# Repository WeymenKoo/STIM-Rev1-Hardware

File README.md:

<!-- Claude: before every commit or push to this repo, update this README first (status line and date, folder table, anything that moved or was added). It is the only project-level document the team and the client read here; keep it short and factual. -->

# STIM Rev 1 hardware (JY063)

UBC ELEC 491 capstone, project JY063. One channel of a four-channel electrical vestibular stimulator:
a ±100 V bootstrapped Howland current pump (the client's STIM board) and our Rev 1 bench prototype of it.

**Status 2026-11-08.** Client-board LTspice model and acceptance tests A1–A7 simulated; bench measurements at ±30 V in
progress. Rev 1 schematic at 2.1.0-dev (PRELIMINARY): DAC (AD5761R), two ADCs (ADS8689), two ISO7741 isolators
with a bypass header and +5 V / +3.3 V rails added 2026-11-07/08 (sheets 10–13); PCB placed, not routed, not yet updated
from the schematic. Safety protection is planned for Rev 2;
Rev 1 is a bench prototype for dummy loads only, not a safety sign-off.

**Handover note (2026-11-08, Weymen away until about Nov 11).** Everything is in this repository; nothing is pending on a
local machine. If you pick this up:
1. Schematic: `02_rev1_channel/Kicad Projects/STIM_Rev1/` (KiCad 10). Read its `README.md` and the `[Unreleased]`
   block of `CHANGELOG.md` first; `Schematic/STIM_Rev1.pdf` is the current plot, `Report/STIM_Rev1-erc.txt` the
   current ERC (0 errors, 7 known warnings). Next KiCad steps: ERC in the GUI, Update PCB from Schematic, then layout.
2. Open decisions (owner Weymen, do not close without him): DAC range vs RG3 on sheet 6; LCSC numbers still TBD
   (TPS7A4901, 32.4k / 17.8k 0603, 1 uF 0603, 2x8 IDC header); ISO7741FDWR is LCSC/JLCPCB-only stock.
3. FPGA interface for CPEN: `02_rev1_channel/ICD_J3.md` (J3 pinout, three chip selects, read-back scaling).
4. Part sourcing snapshot: `.../STIM_Rev1/Documentation/sourcing_converters_isolators_2026-11-07.csv`.
5. Bench: client-board B0 bring-up records under `01_client_board/tests/B0-bringup/` and `01_client_board/bench/`.
Dates that matter: Rev 1 order target Mon Nov 10, hard cutoff Wed Nov 12 (DR1 Dec 1).

| Folder | What is in it |
|---|---|
| `01_client_board/` | LTspice model of the client's STIM board (`model/`), acceptance tests A1–A7, one folder each (`tests/`), bench rig script and wiring (`bench/`), the sim-vs-bench table (`acceptance-tests.md`), deck 2 (`deck/`) |
| `02_rev1_channel/` | Rev 1 analog channel: KiCad project `Kicad Projects/STIM_Rev1/` (own README and CHANGELOG), design definition, FPGA interface contract `ICD_J3.md`, gate simulations G1/G2 (`tests/`) |
| `03_safety_plan/` | Safety planning for Rev 2: FMEA table, safety-loop architecture and its KiCad sketch, deck 1 |
| `04_demo/` | DR1 demo (Dec 1): FPGA waveform CSV → bench and → simulation, same plots |

**Running a simulation.** Open the `.asc` in LTspice 26.x and run it. Every directive is on the sheet; results are
written to the SPICE error log by `.meas` (View → SPICE Error Log). `.raw` and `.log` outputs are not committed;
rerun to regenerate them. Each test folder has a `RECORD.md` with the question, setup and the sim and bench values.

**Number tags.** [DS] datasheet, [H] hand calculation, [L] LTspice, [N] ngspice, [B] bench, [ASSUME] assumption.

Owner: Weymen Koo. Earlier simulation work (Oct 19–25, 2026) is kept offline and is not part of this repository.

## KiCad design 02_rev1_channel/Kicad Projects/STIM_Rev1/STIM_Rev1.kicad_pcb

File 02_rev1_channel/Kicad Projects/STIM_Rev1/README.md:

# STIM Rev 1 Channel (KiCad project)

+/-100 V INA149 Howland current-pump stimulator channel: the minimal analog path for bench bring-up (Rev 1), trips and
latch return in Rev 2. UBC ELEC 491, JY063. Status: **PRELIMINARY** (rev 2.1.0-dev, 2026-11-07), schematic edits from
`SPICE_SIM/02_rev1_channel/REVIEW_2026-10-27.md` applied (D-H); DAC / ADC / isolator sheets 10-13 populated 2026-11-07; PCB placed, not routed (Update PCB from Schematic pending). Bench prototype, dummy loads
only, not a safety sign-off.

**The KiCad files in this repository are the source.** The first capture was generated from the simulation
repository (SPICE_SIM, `4-rev1-design/05_schematic/tools/gen_schematic.py`), but the schematic has been edited
by hand in KiCad since 2.0.0. Do not re-run the generator over this folder.

Part selection and comparison (PhotoMOS, op amps, DC-DC module, connectors, LED, passive sizing):
`Documentation/STIM_Rev1_Parts_Selection.xlsx`, one sheet per part with a summary and charts above the comparison table.
FPGA interface (J3) contract: `SPICE_SIM/02_rev1_channel/ICD_J3.md` (draft until CPEN signs it; **out of date since 2026-11-04**: J3 is now SPI + ENABLE + 3.3 V, see CHANGELOG).

## Specifications

Tags: [N] ngspice, [L] LTspice, [H] hand calc, [DS] datasheet, [B] bench (none yet).

| Parameter | Rev 1 |
|---|---|
| Output | +/-5 mA, 1 mA/V at DAC_BUF (R7 1.00k). U3 gain = 1 + RF3/RG3: **5.02 with RG3 fitted** (Red Pitaya OUT1/OUT2, +/-1 V), 1 with RG3 DNP (+/-5 V DAC) |
| Command ceiling | G = 1: D3/D4 clamp, ~6.3-7.4 mA. G = 5: U3 output saturation at the +/-9 V LDO rails, ~9 mA. DN2540 limiter behind both |
| Compliance | 5 mA into >= 13 kOhm at a 90 V rail, worst case: 13.15 kOhm [N, model-dependent, archive WS1; margin ~1 %, not yet measured] |
| Rails | +/-100 V nominal (90-110 V) on J1; one +12 V on J2; +/-12 V from U32 (A1212S module); +5V (U46, ADC AVDD) and +3V3 (U47, logic / isolator side 2) from +12V_IN on sheet 13. U32 is an isolated part but its COM is GND; the only barrier is the J3 / isolator one (sheet 10): FPGA ground is isolated from board ground, electrodes are not isolated from the board |
| HV input | F1/F2 0451.500MRL 500 mA 125 VDC (rail-to-rail short at +/-100 V exceeds the rating: open item); RSP/RSN 10 Ohm shunts; C2/C3 1 uF 400 V with R23/R24 200k bleeders (tau 0.2 s) |
| Bench supplies | two 30 V supplies in series, midpoint to GND, bias jumpers JP1/JP2 closed (`02_rev1_channel/rev1-minimal-design-definition.md` §5 [N]) |
| Limiter | DN2540 pair + RLIM1, 6.4-8.8 mA [N]. **M1/M2/RLIM1 DNP at assembly**, paired and fitted at bring-up (R2); JP4 bypasses the limiter until then, never at +/-100 V |
| Switches | two AQY214S PhotoMOS (stimulating U4, return U5) driven by ENABLE (R22 100k pull-down = open). JP5/JP6 bypass them (OFF by default); with ENABLE low an ammeter across JP5 measures the stimulating-line current |
| Read-back | I_RETURN_ADC = VMID + 0.2 V/mA; V_ELEC_ADC = VMID + V_elec/101; VMID_REF 1.66 V; read by two ADS8689 (16-bit, 0-5.12 V range): U41 on I_RETURN_ADC, U42 on V_ELEC_ADC, sheet 12. VMID_REF is measured once on TP29, not digitised |
| FPGA connector J3 | 2x8 IDC: 1 +3V3_FPGA, 3 SPI_SCLK, 5 SPI_MOSI, 7 SPI_MISO, 9 SPI_CS_DAC, 11 SPI_CS_ADC, 13 ENABLE, 15 SPI_CS_ADC2, even pins GND_FPGA. Isolated by U43 ISO7741FDWR (ENABLE, SCLK, MOSI; default low) and U44 ISO7741DWR (CS_DAC, CS_ADC, CS_ADC2, MISO back; default high); J5 is the board-side twin for the JP7 bypass; one spare reverse channel (FAULT_N, TP38). `ICD_J3.md` rewritten 2026-11-07 |
| Command DAC | U40 AD5761RBRUZ, +/-5 V range on +/-12 V, 2.5 V internal reference, SPI shared with the ADC (CS_DAC); DAC_CMD +/-5 V -> RG3 DNP (G = 1) or range +/-3 V with RG3 fitted (open) |
| Board | JLCPCB 4-layer JLC04161H-7628, 1.6 mm, Economic PCBA (top side). Target outline <= 100 x 100 mm (4-layer promo tier) |
| Parts | 175 references: 133 parts (M1, M2, RLIM1 DNP), 38 test loops (TP2, TP4-TP40), 4 mounting holes. Power sheets 3, 4 and 13 export their rails as ports; the rail symbols sit on the cover. Extended-part types added 2026-11-07/08: ISO7741DWR, ISO7741FDWR, AD5761RBRUZ, ADS8689IPWR (4); TPS7A4901 reused |

## Pages

1. Doc - Cover (`STIM_Rev1.kicad_sch`)
2. Doc - Revision History (`revision-history.kicad_sch`)
3. Power - HV Input & Fusing (`power-hv-input.kicad_sch`)
4. Power - Aux Input & +/-9 V LDOs (`power-aux-input.kicad_sch`)
5. Interface - FPGA (`interface-fpga.kicad_sch`)
6. Analog - Input Clamp & Buffer (`analog-clamp-buffer.kicad_sch`)
7. Analog - Howland Current Pump (`analog-current-pump.kicad_sch`)
8. Output - Limiter & PhotoMOS (`output-limiter-photomos.kicad_sch`)
9. Sense - Feedback to ADC (`sense-feedback-adc.kicad_sch`)
10. Interface - SPI Isolator (`interface-spi-isolator.kicad_sch`) - U43/U44 ISO7741, J5 bypass header, JP7
11. Interface - DAC Command (`interface-dac-command.kicad_sch`) - U40 AD5761R
12. Interface - ADC Read-back (`interface-adc-readback.kicad_sch`) - U41 / U42 ADS8689 (I and V)
13. Power - Converter Rails (`power-converter-rails.kicad_sch`) - U46 +5V, U47 +3V3

## Directory structure

```
STIM_Rev1
├── CHANGELOG.md     # Keep a Changelog; the Revision History page is generated from it
├── Templates        # KDT_Template_GIT.kicad_wks title block (nguyen-v/KDT_Hierarchical_KiBot, MIT)
├── Report           # ERC report (DRC after layout)
├── Testing/Testpoints   # test-point tables (after layout)
├── lib
│   ├── lib_sym      # STIM_Rev1.kicad_sym: every symbol of the design
│   ├── lib_fp       # STIM_Rev1.pretty: every footprint of the design
│   └── 3d_models    # STEP models
├── Simulation
│   ├── models       # SPICE models used by the symbols' simulation fields
│   └── figures      # simulation figures
├── Computations     # rev1_hand_calcs.md (the Oct 24 PDF is in _archive/)
├── Documentation    # parts selection workbook (xlsx), sourcing snapshots (csv)
├── tools            # one-shot generator that drew sheets 10-13 (record only, do not re-run)
├── Schematic        # PDF of the schematic
├── Manufacturing
│   ├── Assembly     # BoM, CPL (after layout, Fabrication Toolkit)
│   └── Fabrication  # Gerbers, drill (after layout)
└── Images           # renders
```

## Design rules

4-layer JLCPCB stackup and HV rules in `STIM_Rev1.kicad_dru`, with sources: SPICE_SIM `4-rev1-design/07_pcb/design-rules-research.md`.

## Format and versioning

Layout follows the EPFL Xplore AMULET controller schematics and the KDT_Hierarchical_KiBot template by the same
author (https://github.com/nguyen-v/KDT_Hierarchical_KiBot): folder tree, title block (`Templates/`, MIT licence
alongside), text variables (`PROJECT_NAME`, `BOARD_NAME`, `COMPANY`, `DESIGNER`, `VARIANT`, `REVISION`,
`RELEASE_DATE`, `SHEET_NAME_n`, `RELEASE_TITLE_x` / `RELEASE_BODY_x`), `CHANGELOG.md` with an `[Unreleased]`
section, and the variant vocabulary DRAFT / PRELIMINARY / CHECKED / RELEASED. Versions are semantic versioning
applied to hardware (https://www.maskset.net/blog/2023/02/26/semantic-versioning-for-hardware/): MAJOR incompatible
interface or form factor, MINOR compatible circuit / BoM / stackup change, PATCH documentation only. KiBot CI from the
template is not set up here.

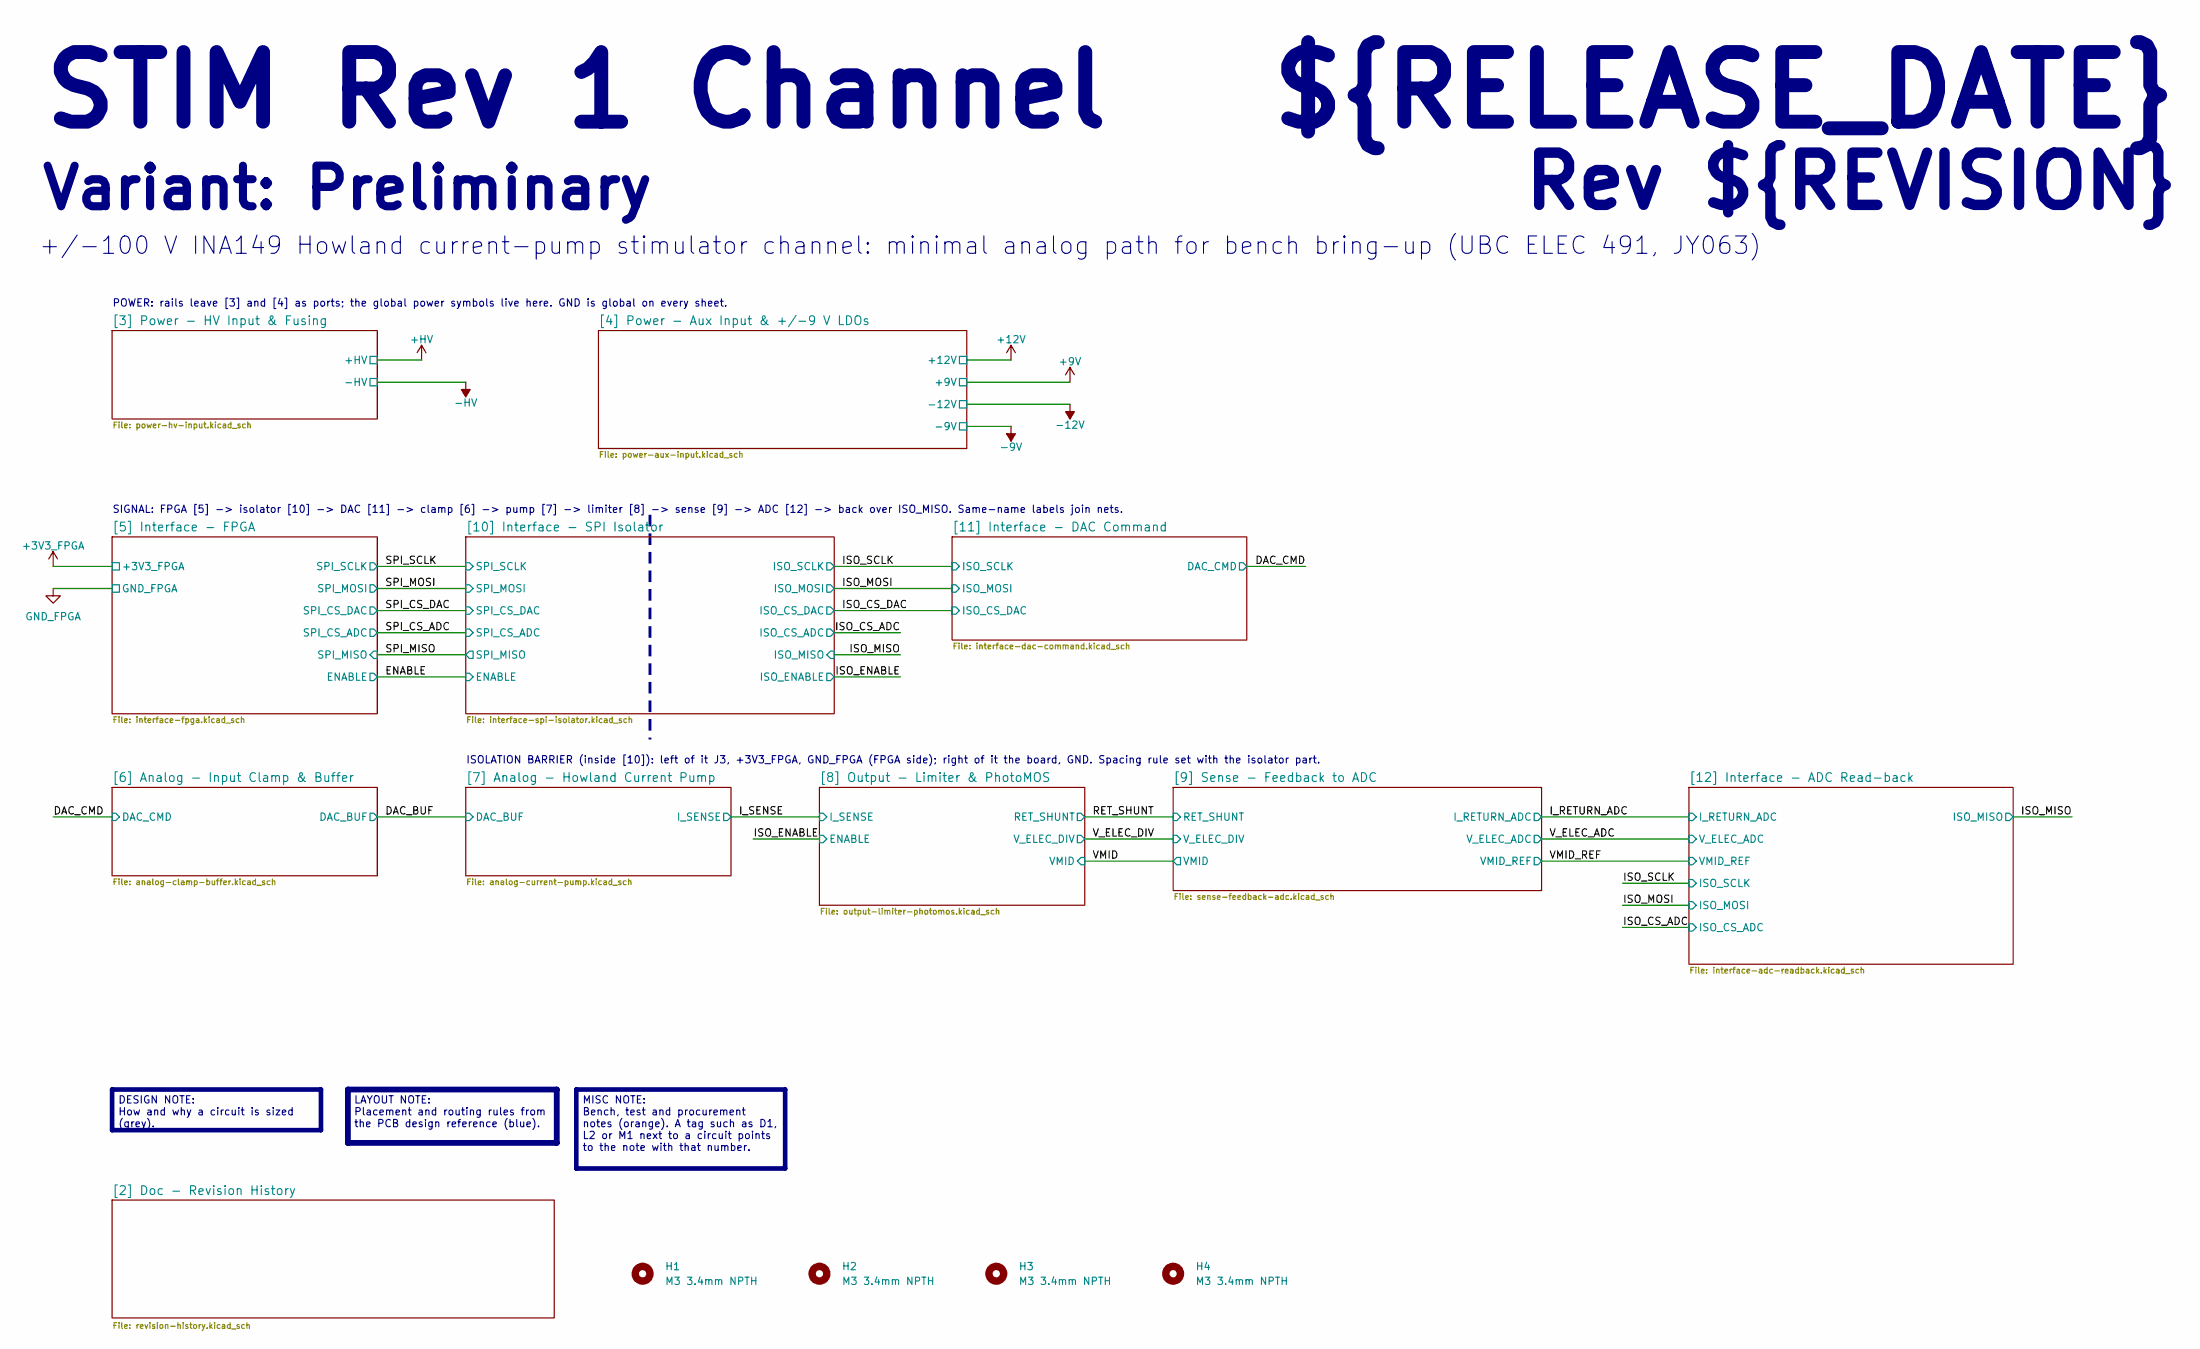
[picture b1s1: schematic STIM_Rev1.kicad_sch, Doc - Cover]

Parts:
H1, H2, H3, H4: M3 3.4mm NPTH; MountingHole_3.4mm_M3_Keepout6.5mm

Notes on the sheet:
Variant: Preliminary
${RELEASE_DATE}
STIM Rev 1 Channel
+/-100 V INA149 Howland current-pump stimulator channel: minimal analog path for bench bring-up (UBC ELEC 491, JY063)
Rev ${REVISION}
MISC NOTE: Bench, test and procurement notes (orange). A tag such as D1, L2 or M1 next to a circuit points to the note with that number.
LAYOUT NOTE: Placement and routing rules from the PCB design reference (blue).
DESIGN NOTE: How and why a circuit is sized (grey).
POWER: rails leave [3] and [4] as ports; the global power symbols live here. GND is global on every sheet.
ISOLATION BARRIER (inside [10]): left of it J3, +3V3_FPGA, GND_FPGA (FPGA side); right of it the board, GND. Spacing rule set with the isolator part.
SIGNAL: FPGA [5] -> isolator [10] -> DAC [11] -> clamp [6] -> pump [7] -> limiter [8] -> sense [9] -> ADC [12] -> back over ISO_MISO. Same-name labels join nets.

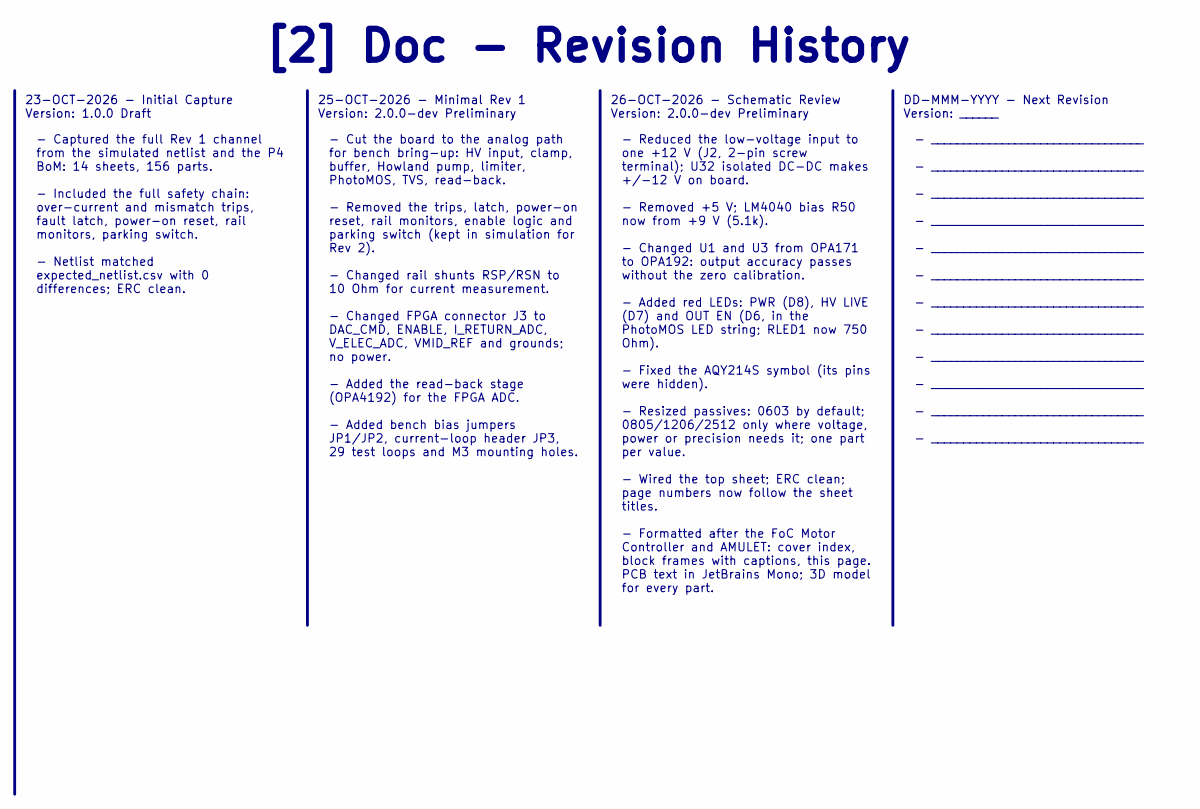
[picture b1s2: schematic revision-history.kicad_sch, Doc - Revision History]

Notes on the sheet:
23-OCT-2026 - Initial Capture Version: 1.0.0 Draft
25-OCT-2026 - Minimal Rev 1 Version: 2.0.0-dev Preliminary
- Cut the board to the analog path for bench bring-up: HV input, clamp, buffer, Howland pump, limiter, PhotoMOS, TVS, read-back. - Removed the trips, latch, power-on reset, rail monitors, enable logic and parking switch (kept in simulation for Rev 2). - Changed rail shunts RSP/RSN to 10 Ohm for cur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
26-OCT-2026 - Schematic Review Version: 2.0.0-dev Preliminary
[2] Doc - Revision History
- _________________________________ - _________________________________ - _________________________________ - _________________________________ - _________________________________ - _________________________________ - _________________________________ - _________________________________ - _________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
DD-MMM-YYYY - Next Revision Version: ______
- Captured the full Rev 1 channel from the simulated netlist and the P4 BoM: 14 sheets, 156 parts. - Included the full safety chain: over-current and mismatch trips, fault latch, power-on reset, rail monitors, parking switch. - Netlist matched expected_netlist.csv with 0 differences; ERC clean.
- Reduced the low-voltage input to one +12 V (J2, 2-pin screw terminal); U32 isolated DC-DC makes +/-12 V on board. - Removed +5 V; LM4040 bias R50 now from +9 V (5.1k). - Changed U1 and U3 from OPA171 to OPA192: output accuracy passes without the zero calibration. - Added red LEDs: PWR (D8), HV LI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

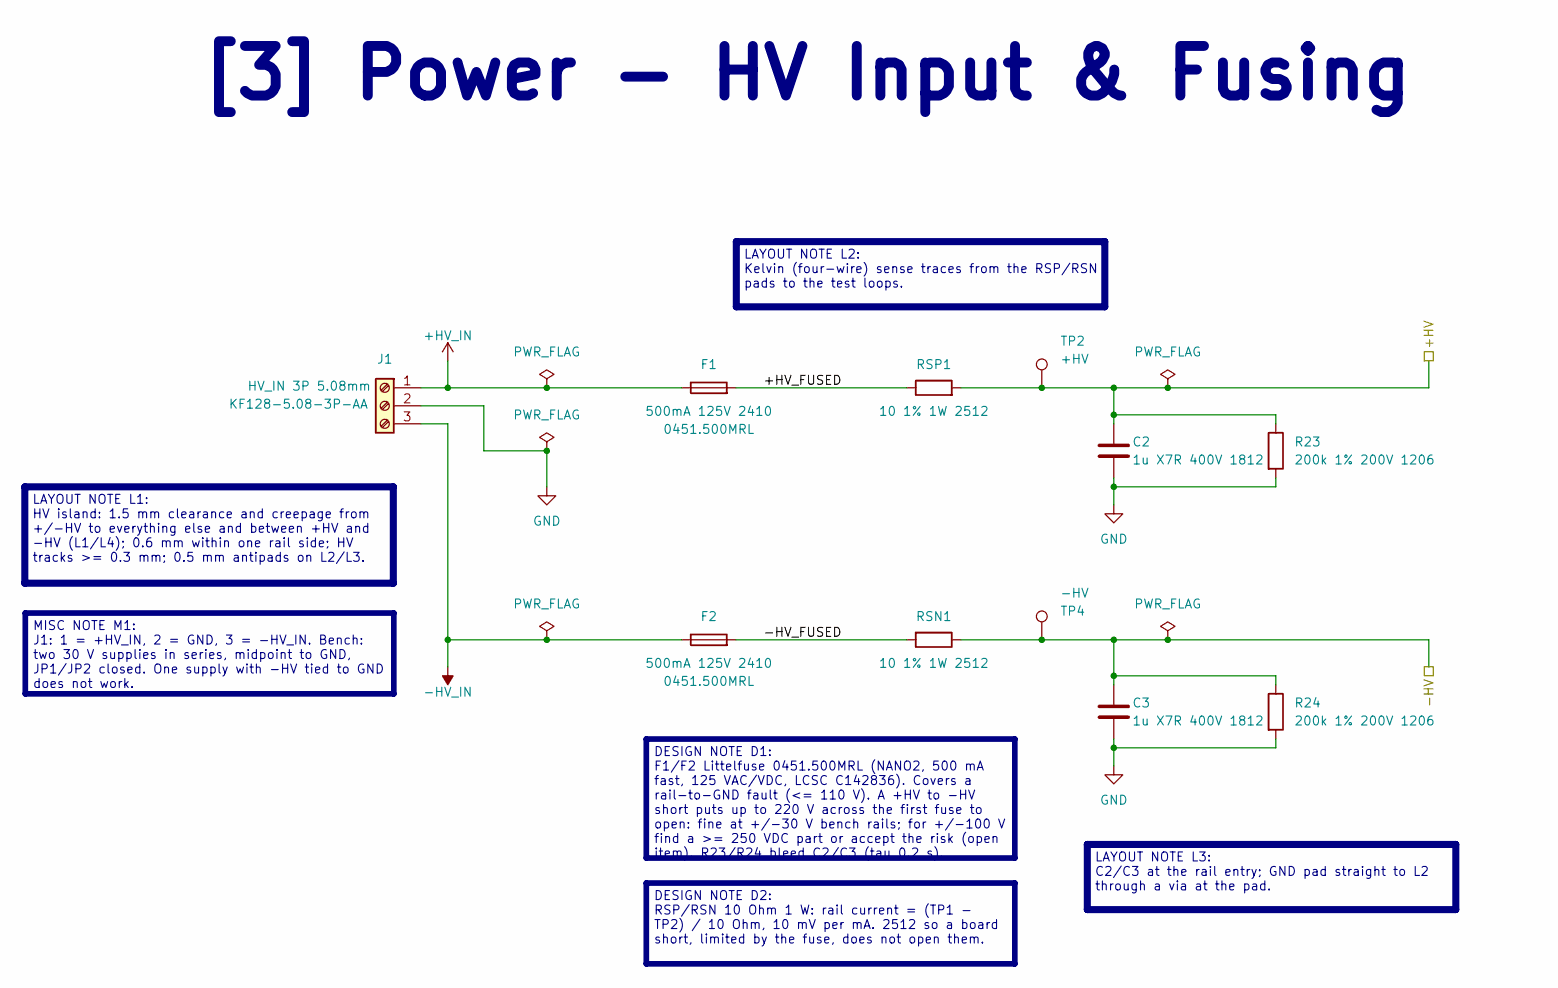
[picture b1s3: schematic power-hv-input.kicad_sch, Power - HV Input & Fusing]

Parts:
C2, C3: 1u X7R 400V 1812; C_1812_4532Metric; MPN FE2CX105M501LFL; LCSC C19267793
F1, F2: 500mA 125V 2410; Fuse_2410_6125Metric_SST; MPN 0451.500MRL; LCSC C142836
J1: HV_IN 3P 5.08mm; TerminalBlock_Phoenix_MKDS-1,5-3-5.08_1x03_P5.08mm_Horizont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; MPN KF128-5.08-3P-AA; LCSC C474953
R23, R24: 200k 1% 200V 1206; R_1206_3216Metric; MPN 1206W4F2003T5E; LCSC C17954
RSN1: 10 1% 1W 2512; R_2512_6332Metric; MPN 25121WF100JT4E; LCSC C47019
RSP1: 10 1% 1W 2512; R_2512_6332Metric; MPN 25121WF100JT4E; LCSC C47019
TP2: +HV; TestPoint_Keystone_5000-5004_Miniature
TP4: -HV; TestPoint_Keystone_5000-5004_Miniature

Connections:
+HV: C2.1, R23.1, RSP1.2, TP2.1 (1_1); also elsewhere on the board
+HV_IN: F1.1, J1.1; also elsewhere on the board
-HV: C3.1, R24.1, RSN1.1, TP4.1 (1_1); also elsewhere on the board
-HV_IN: F2.1, J1.3; also elsewhere on the board
/[3] Power - HV Input & Fusing/+HV_FUSED: F1.2, RSP1.1
/[3] Power - HV Input & Fusing/-HV_FUSED: F2.2, RSN1.2

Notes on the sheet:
[3] Power - HV Input & Fusing
DESIGN NOTE D1: F1/F2 Littelfuse 0451.500MRL (NANO2, 500 mA fast, 125 VAC/VDC, LCSC C142836). Covers a rail-to-GND fault (<= 110 V). A +HV to -HV short puts up to 220 V across the first fuse to open: fine at +/-30 V bench rails; for +/-100 V find a >= 250 VDC part or accept the risk (open item). R2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
DESIGN NOTE D2: RSP/RSN 10 Ohm 1 W: rail current = (TP1 - TP2) / 10 Ohm, 10 mV per mA. 2512 so a board short, limited by the fuse, does not open them.
LAYOUT NOTE L1: HV island: 1.5 mm clearance and creepage from +/-HV to everything else and between +HV and -HV (L1/L4); 0.6 mm within one rail side; HV tracks >= 0.3 mm; 0.5 mm antipads on L2/L3.
LAYOUT NOTE L3: C2/C3 at the rail entry; GND pad straight to L2 through a via at the pad.
LAYOUT NOTE L2: Kelvin (four-wire) sense traces from the RSP/RSN pads to the test loops.
MISC NOTE M1: J1: 1 = +HV_IN, 2 = GND, 3 = -HV_IN. Bench: two 30 V supplies in series, midpoint to GND, JP1/JP2 closed. One supply with -HV tied to GND does not work.

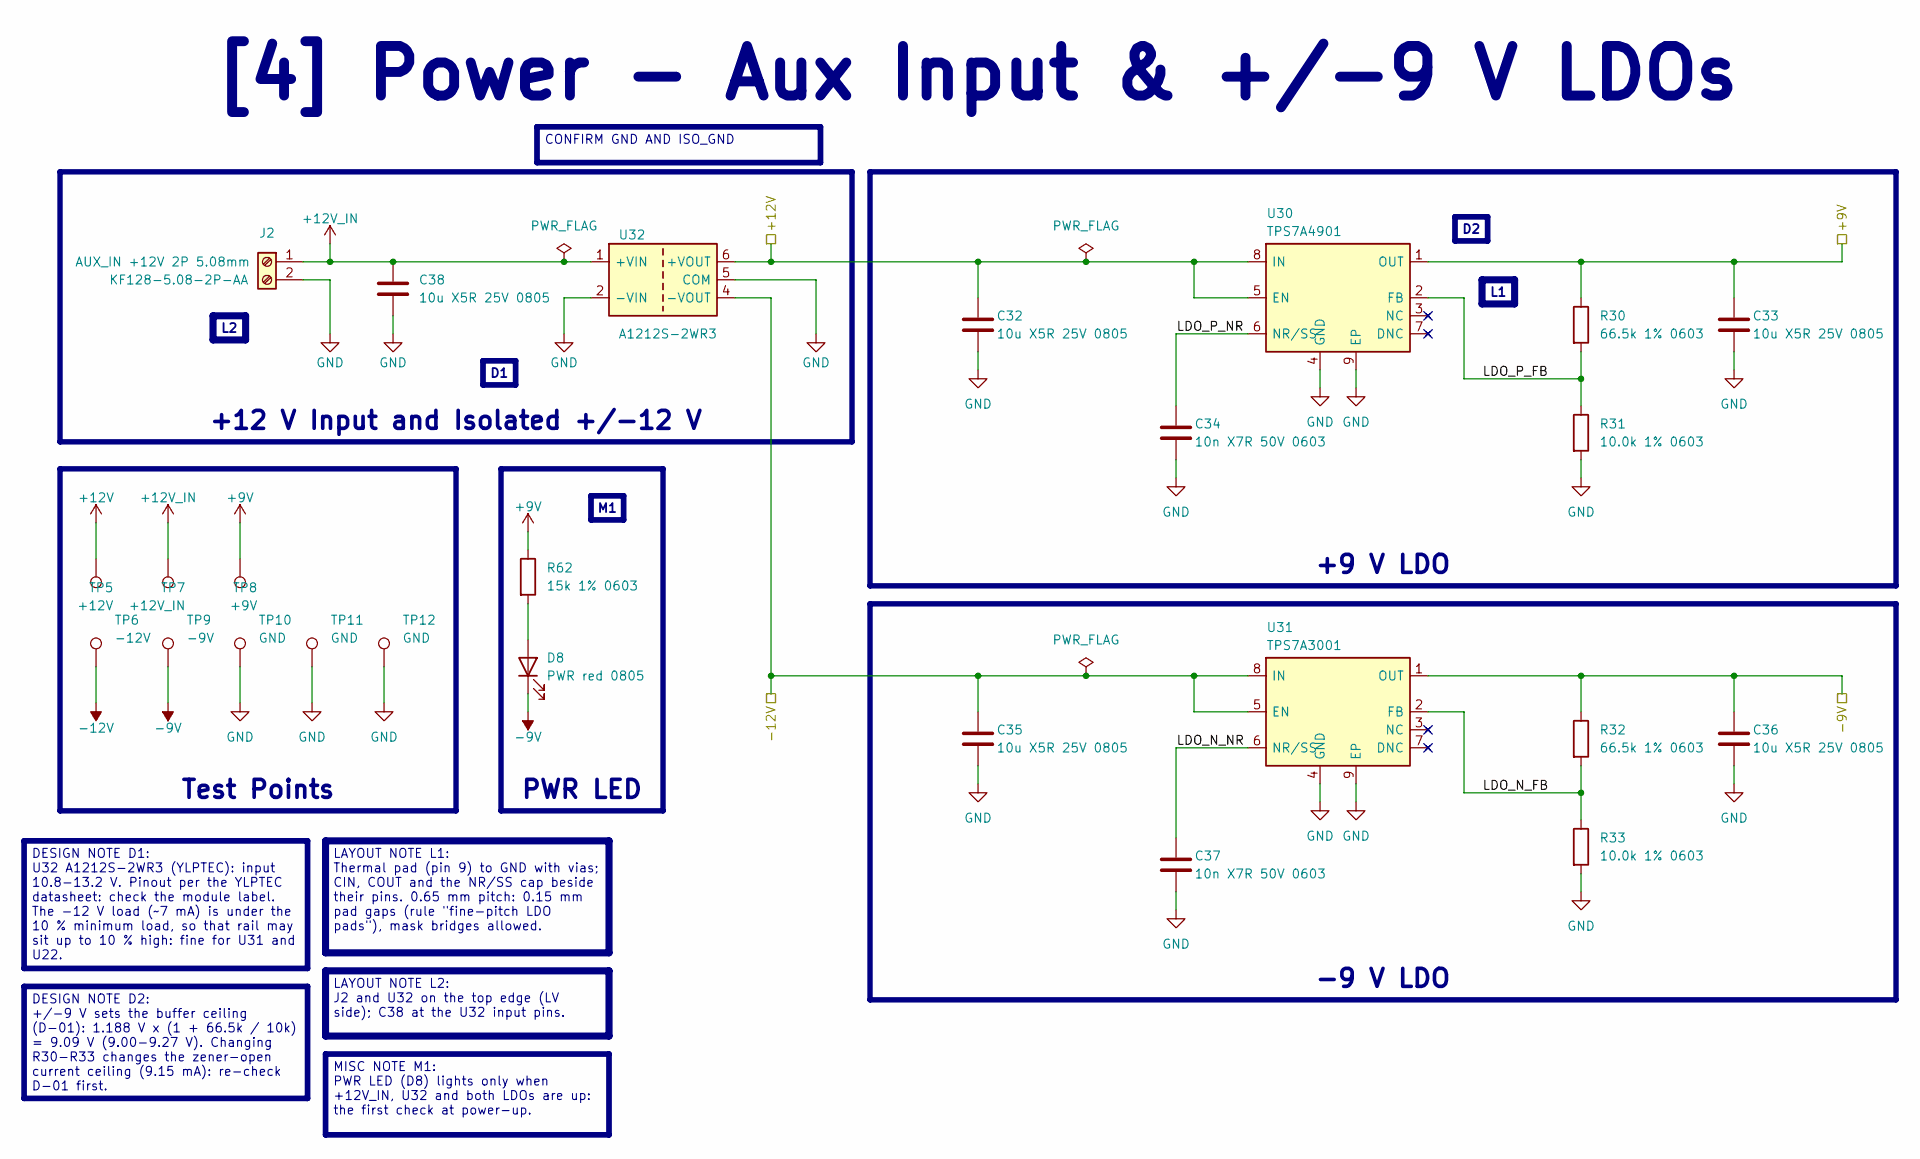
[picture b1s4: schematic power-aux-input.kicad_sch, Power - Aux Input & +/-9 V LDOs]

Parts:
C32, C33, C35, C36, C38: 10u X5R 25V 0805; C_0805_2012Metric; MPN CL21A106KAYNNNE; LCSC C15850
C34, C37: 10n X7R 50V 0603; C_0603_1608Metric; MPN CL10B103KB8NNNC; LCSC C1589
D8: PWR red 0805; LED_0805_2012Metric; MPN NCD0805R1; LCSC C84256
J2: AUX_IN +12V 2P 5.08mm; TerminalBlock_Phoenix_MKDS-1,5-2-5.08_1x02_P5.08mm_Horizont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; MPN KF128-5.08-2P-AA; LCSC C474952
R30, R32: 66.5k 1% 0603; R_0603_1608Metric; MPN 0603WAF6652T5E; LCSC C23225
R31, R33: 10.0k 1% 0603; R_0603_1608Metric; MPN 0603WAF1002T5E; LCSC C25804
R62: 15k 1% 0603; R_0603_1608Metric; MPN 0603WAF1502T5E; LCSC C22809
TP5: +12V; TestPoint_Keystone_5000-5004_Miniature
TP6: -12V; TestPoint_Keystone_5000-5004_Miniature
TP7: +12V_IN; TestPoint_Keystone_5000-5004_Miniature
TP8: +9V; TestPoint_Keystone_5000-5004_Miniature
TP9: -9V; TestPoint_Keystone_5000-5004_Miniature
TP10, TP11, TP12: GND; TestPoint_Keystone_5000-5004_Miniature
U30: TPS7A4901; Texas_DGN0008D_VSSOP-8-1EP_3x3mm_P0.65mm_EP2x2.94mm_Mask1.5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
U31: TPS7A3001; Texas_DGN0008D_VSSOP-8-1EP_3x3mm_P0.65mm_EP2x2.94mm_Mask1.5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
U32: A1212S-2WR3; Converter_DCDC_A_S-2WR3_SIP-6_P2.54mm; MPN A1212S-2WR3; LCSC C5369434

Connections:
+9V: C33.1, R30.1, R62.1, TP8.1 (1_1), U30.1 (OUT); also elsewhere on the board
+12V: C32.1, TP5.1 (1_1), U30.5 (EN), U30.8 (IN), U32.6 (+VOUT); also elsewhere on the board
+12V_IN: C38.1, J2.1, TP7.1 (1_1), U32.1 (+VIN)
-9V: C36.1, D8.1 (K), R32.1, TP9.1 (1_1), U31.1 (OUT); also elsewhere on the board
-12V: C35.1, TP6.1 (1_1), U31.5 (EN), U31.8 (IN), U32.4 (-VOUT); also elsewhere on the board
/[4] Power - Aux Input & +/-9 V LDOs/LDO_N_FB: R32.2, R33.1, U31.2 (FB)
/[4] Power - Aux Input & +/-9 V LDOs/LDO_N_NR: C37.1, U31.6 (NR/SS)
/[4] Power - Aux Input & +/-9 V LDOs/LDO_P_FB: R30.2, R31.1, U30.2 (FB)
/[4] Power - Aux Input & +/-9 V LDOs/LDO_P_NR: C34.1, U30.6 (NR/SS)
unnamed: D8.2 (A), R62.2

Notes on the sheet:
Test Points
PWR LED
-9 V LDO
CONFIRM GND AND ISO_GND
+9 V LDO
LAYOUT NOTE L1: Thermal pad (pin 9) to GND with vias; CIN, COUT and the NR/SS cap beside their pins. 0.65 mm pitch: 0.15 mm pad gaps (rule "fine-pitch LDO pads"), mask bridges allowed.
LAYOUT NOTE L2: J2 and U32 on the top edge (LV side); C38 at the U32 input pins.
DESIGN NOTE D1: U32 A1212S-2WR3 (YLPTEC): input 10.8-13.2 V. Pinout per the YLPTEC datasheet: check the module label. The -12 V load (~7 mA) is under the 10 % minimum load, so that rail may sit up to 10 % high: fine for U31 and U22.
MISC NOTE M1: PWR LED (D8) lights only when +12V_IN, U32 and both LDOs are up: the first check at power-up.
DESIGN NOTE D2: +/-9 V sets the buffer ceiling (D-01): 1.188 V x (1 + 66.5k / 10k) = 9.09 V (9.00-9.27 V). Changing R30-R33 changes the zener-open current ceiling (9.15 mA): re-check D-01 first.
[4] Power - Aux Input & +/-9 V LDOs
+12 V Input and Isolated +/-12 V

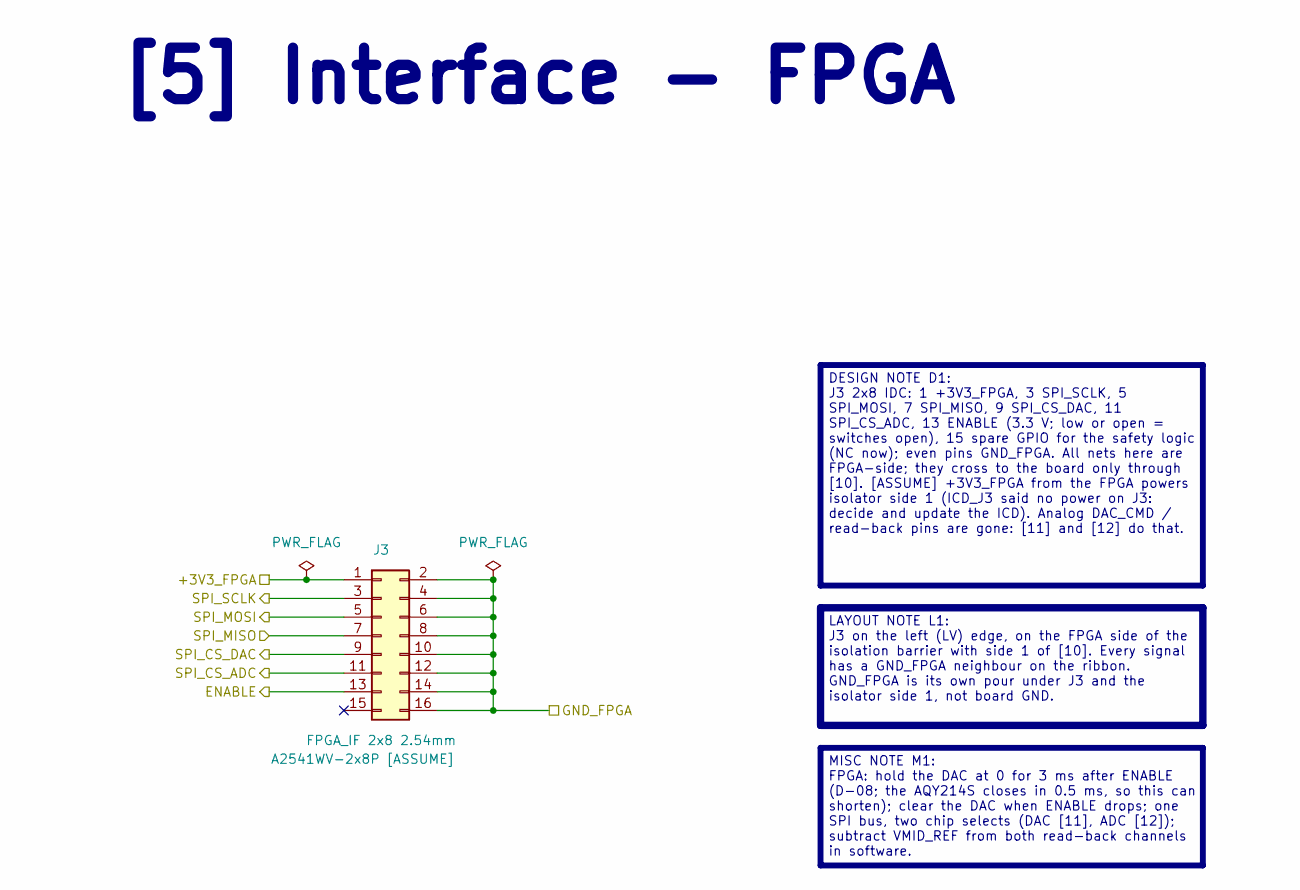
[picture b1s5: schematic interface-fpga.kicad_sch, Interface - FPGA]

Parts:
J3: FPGA_IF 2x8 2.54mm; IDC-Header_2x08_P2.54mm_Vertical; MPN A2541WV-2x8P [ASSUME]; JLC Extended

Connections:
/ENABLE: J3.3; also elsewhere on the board
/I_RETURN_ADC: J3.5; also elsewhere on the board
/VMID_REF: J3.9; also elsewhere on the board
/V_ELEC_ADC: J3.7; also elsewhere on the board

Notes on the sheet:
[5] Interface - FPGA
LAYOUT NOTE L1: J3 on the left (LV) edge, on the FPGA side of the isolation barrier with side 1 of [10]. Every signal has a GND_FPGA neighbour on the ribbon. GND_FPGA is its own pour under J3 and the isolator side 1, not board GND.
DESIGN NOTE D1: J3 2x8 IDC: 1 +3V3_FPGA, 3 SPI_SCLK, 5 SPI_MOSI, 7 SPI_MISO, 9 SPI_CS_DAC, 11 SPI_CS_ADC, 13 ENABLE (3.3 V; low or open = switches open), 15 spare GPIO for the safety logic (NC now); even pins GND_FPGA. All nets here are FPGA-side; they cross to the board only through [10]. [ASSUME]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
MISC NOTE M1: FPGA: hold the DAC at 0 for 3 ms after ENABLE (D-08; the AQY214S closes in 0.5 ms, so this can shorten); clear the DAC when ENABLE drops; one SPI bus, two chip selects (DAC [11], ADC [12]); subtract VMID_REF from both read-back channels in software.

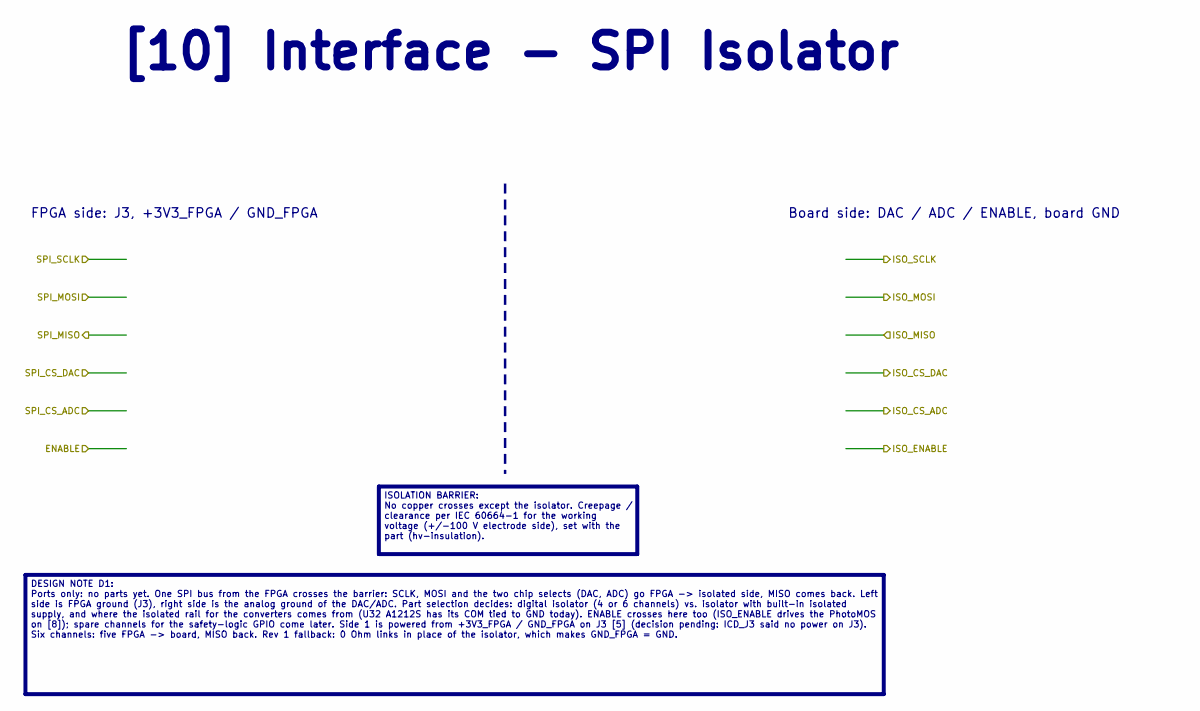
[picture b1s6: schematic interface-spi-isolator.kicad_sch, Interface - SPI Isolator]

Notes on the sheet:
ISOLATION BARRIER: No copper crosses except the isolator. Creepage / clearance per IEC 60664-1 for the working voltage (+/-100 V electrode side), set with the part (hv-insulation).
FPGA side: J3, +3V3_FPGA / GND_FPGA
Board side: DAC / ADC / ENABLE, board GND
DESIGN NOTE D1: Ports only: no parts yet. One SPI bus from the FPGA crosses the barrier: SCLK, MOSI and the two chip selects (DAC, ADC) go FPGA -> isolated side, MISO comes back. Left side is FPGA ground (J3), right side is the analog ground of the DAC/ADC. Part selection decides: digital isolator 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
[10] Interface - SPI Isolator

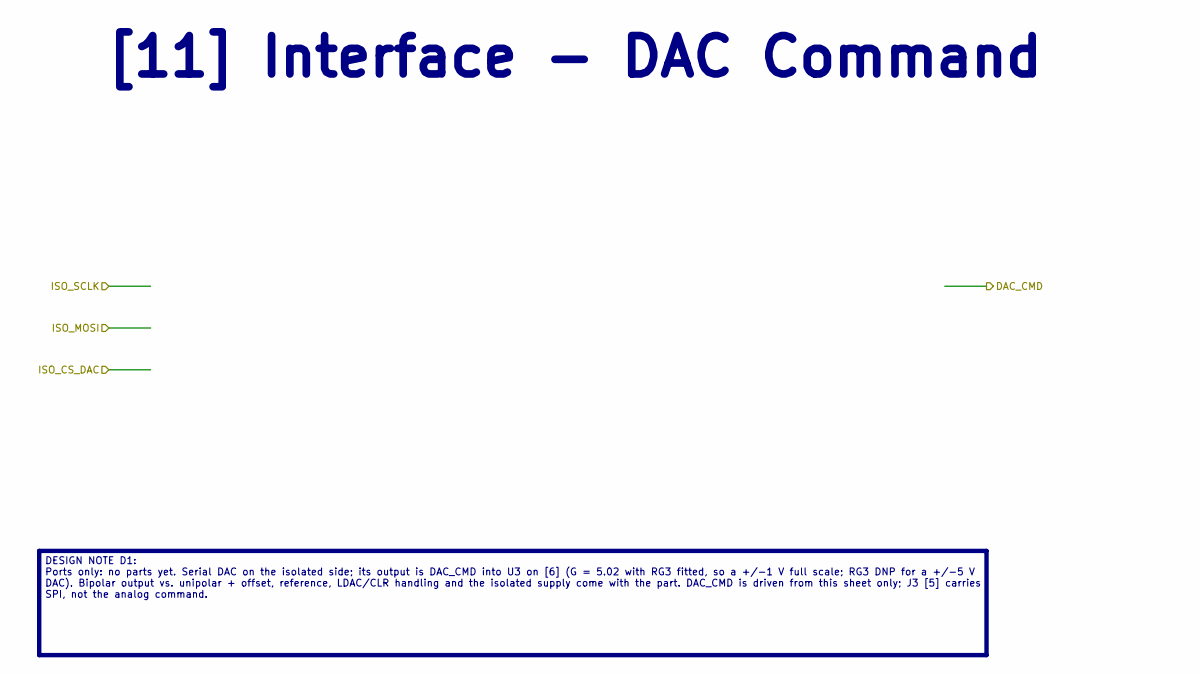
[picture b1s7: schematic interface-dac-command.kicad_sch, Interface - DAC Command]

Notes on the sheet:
[11] Interface - DAC Command
DESIGN NOTE D1: Ports only: no parts yet. Serial DAC on the isolated side; its output is DAC_CMD into U3 on [6] (G = 5.02 with RG3 fitted, so a +/-1 V full scale; RG3 DNP for a +/-5 V DAC). Bipolar output vs. unipolar + offset, reference, LDAC/CLR handling and the isolated supply come with the part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

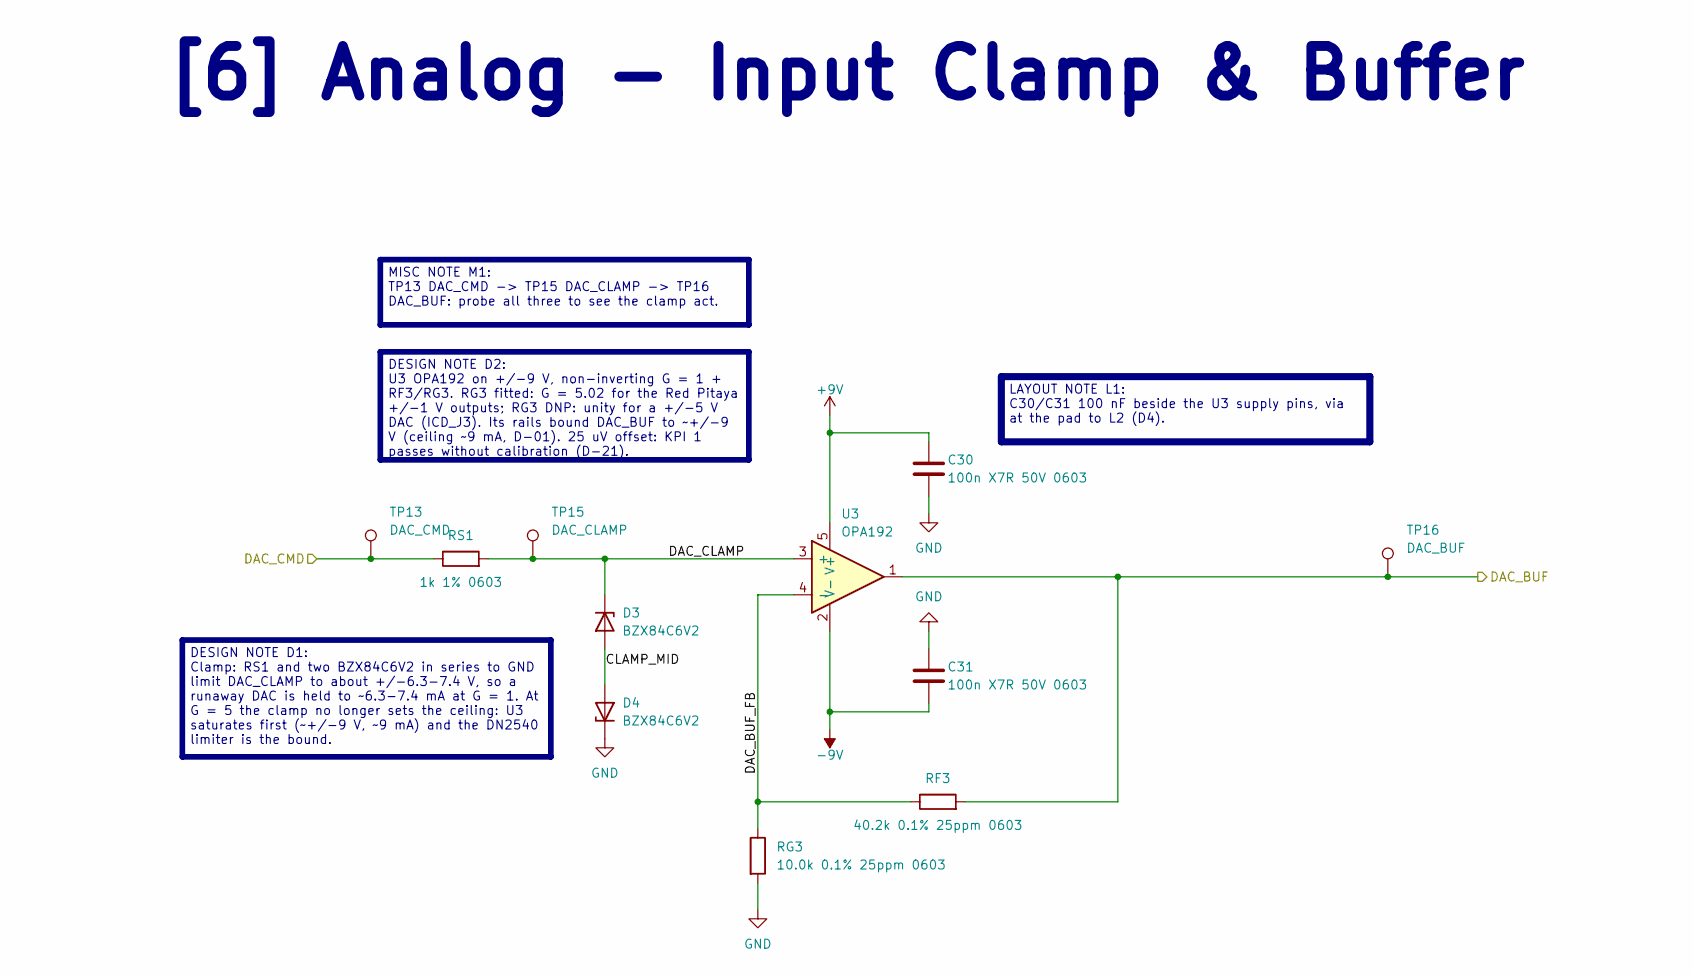
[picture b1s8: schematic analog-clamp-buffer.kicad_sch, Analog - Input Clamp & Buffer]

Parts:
C30, C31: 100n X7R 50V 0603; C_0603_1608Metric; MPN CL10B104KB8NNNC; LCSC C1591
D3, D4: BZX84C6V2; SOT-23; MPN BZX84C6V2LT1G; LCSC C82470
RF3: 40.2k 0.1% 25ppm 0603; R_0603_1608Metric; MPN RT0603BRD0740K2L; LCSC C723489
RG3: 10.0k 0.1% 25ppm 0603; R_0603_1608Metric; MPN RT0603BRD0710KL; LCSC C95204
RS1: 1k 1% 0603; R_0603_1608Metric; MPN 0603WAF1001T5E; LCSC C21190
TP13: DAC_CMD; TestPoint_Keystone_5000-5004_Miniature
TP15: DAC_CLAMP; TestPoint_Keystone_5000-5004_Miniature
TP16: DAC_BUF; TestPoint_Keystone_5000-5004_Miniature
U3: OPA192; SOT-23-5; MPN OPA192IDBVR; LCSC C139648

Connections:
+9V: C30.1, U3.5 (V+); also elsewhere on the board
-9V: C31.1, U3.2 (V-); also elsewhere on the board
/DAC_BUF: RF3.2, TP16.1 (1_1), U3.1; also elsewhere on the board
/[6] Analog - Input Clamp & Buffer/CLAMP_MID: D3.1 (A), D4.1 (A)
/[6] Analog - Input Clamp & Buffer/DAC_BUF_FB: RF3.1, RG3.1, U3.4 (-)
/[6] Analog - Input Clamp & Buffer/DAC_CLAMP: D3.3 (K), RS1.2, TP15.1 (1_1), U3.3 (+)

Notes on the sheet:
[6] Analog - Input Clamp & Buffer
LAYOUT NOTE L1: C30/C31 100 nF beside the U3 supply pins, via at the pad to L2 (D4).
DESIGN NOTE D1: Clamp: RS1 and two BZX84C6V2 in series to GND limit DAC_CLAMP to about +/-6.3-7.4 V, so a runaway DAC is held to ~6.3-7.4 mA at G = 1. At G = 5 the clamp no longer sets the ceiling: U3 saturates first (~+/-9 V, ~9 mA) and the DN2540 limiter is the bound.
MISC NOTE M1: TP13 DAC_CMD -> TP15 DAC_CLAMP -> TP16 DAC_BUF: probe all three to see the clamp act.
DESIGN NOTE D2: U3 OPA192 on +/-9 V, non-inverting G = 1 + RF3/RG3. RG3 fitted: G = 5.02 for the Red Pitaya +/-1 V outputs; RG3 DNP: unity for a +/-5 V DAC (ICD_J3). Its rails bound DAC_BUF to ~+/-9 V (ceiling ~9 mA, D-01). 25 uV offset: KPI 1 passes without calibration (D-21).

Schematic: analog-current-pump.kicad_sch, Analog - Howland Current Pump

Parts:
C1: 100n X7R 250V 1206; C_1206_3216Metric; MPN TCC1206X7R104M251FT; LCSC C282822
C40: 100n X7R 50V 0603; C_0603_1608Metric; MPN CL10B104KB8NNNC; LCSC C1591
D1, D2: BAS16; SOT-23; MPN BAS16 A6; LCSC C8489
JP1, JP2: JP 1x2; PinHeader_1x02_P2.54mm_Vertical
Q1: MJD350; TO-252-2; MPN MJD350-13; LCSC C460225
Q2: MJD340; TO-252-2; MPN MJD340-13; LCSC C443830
R1, R2, R5, R6: 44.2k 1% 200V 1206; R_1206_3216Metric; MPN CL1206FN44K2PS; LCSC C53284084
R3, R4: 14.3k 1% 0805; R_0805_2012Metric; MPN 0805W8F1432T5E; LCSC C17456
R7: 1.00k 0.1% 25ppm 0805; R_0805_2012Metric; MPN RT0805BRD071KL; LCSC C110774
RB1, RB2: 41.2k 1% 200V 1206; R_1206_3216Metric; MPN 1206W4F4122T5E; LCSC C247267
TP17: PUMP_OUT; TestPoint_Keystone_5000-5004_Miniature
TP18: PUMP_REF; TestPoint_Keystone_5000-5004_Miniature
TP19, TP20: PUMP_V+; TestPoint_Keystone_5000-5004_Miniature
TP21: I_SENSE; TestPoint_Keystone_5000-5004_Miniature
U1: OPA192; SOT-23-5; MPN OPA192IDBVR; LCSC C139648
U2: INA149; SOIC-8_3.9x4.9mm_P1.27mm; MPN INA149AIDR; LCSC C183089

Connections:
+HV: JP1.1 (A), Q2.2 (C), R1.1; also elsewhere on the board
-HV: JP2.2 (B), Q1.2 (C), R6.2; also elsewhere on the board
/DAC_BUF: U2.3 (+IN); also elsewhere on the board
/[7] Analog - Howland Current Pump/BENCH_BIAS_N: JP2.1 (A), RB2.1
/[7] Analog - Howland Current Pump/BENCH_BIAS_P: JP1.2 (B), RB1.1
/[7] Analog - Howland Current Pump/BIAS_D2_R4: D2.3 (K), R4.1
/[7] Analog - Howland Current Pump/BIAS_R1_R2: R1.2, R2.1
/[7] Analog - Howland Current Pump/BIAS_R3_D1: D1.1 (A), R3.2
/[7] Analog - Howland Current Pump/BIAS_R5_R6: R5.2, R6.1
/[7] Analog - Howland Current Pump/I_SENSE: R7.2, TP21.1 (1_1), U1.3 (+); also elsewhere on the board
/[7] Analog - Howland Current Pump/PUMP_OUT: D1.3 (K), D2.1 (A), R7.1, TP17.1 (1_1), U2.6 (VOUT); also elsewhere on the board
/[7] Analog - Howland Current Pump/PUMP_REF: TP18.1 (1_1), U1.1, U1.4 (-), U2.1 (REF_B), U2.5 (REF_A)
/[7] Analog - Howland Current Pump/PUMP_V+: C40.1, Q2.3 (E), TP19.1 (1_1), U1.5 (V+), U2.7 (V+)
/[7] Analog - Howland Current Pump/PUMP_V-: C40.2, Q1.3 (E), TP20.1 (1_1), U1.2 (V-), U2.4 (V-)
/[7] Analog - Howland Current Pump/Q1_BASE: C1.2, Q1.1 (B), R4.2, R5.1, RB2.2; also elsewhere on the board
/[7] Analog - Howland Current Pump/Q2_BASE: C1.1, Q2.1 (B), R2.2, R3.1, RB1.2; also elsewhere on the board

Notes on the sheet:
MISC NOTE M2: TP17 PUMP_OUT, TP18 PUMP_REF, TP19/TP20 floating rails (span >= 4.5 V), TP21 I_SENSE: all float up to +/-110 V; use a differential or isolated probe.
MISC NOTE M1: JP1/JP2 bench bias: CLOSE at +/-30 V or below; OPEN at +/-100 V (RB1/RB2 would see ~190 V, ~0.9 W in a 0.25 W part).
LAYOUT NOTE L2: C40 across PUMP_V+ / PUMP_V- right at U2 pins 7 and 4: the floating rails decouple to each other, not to GND.
LAYOUT NOTE L1: Q1/Q2 DPAK: >= 300 mm^2 L1 pour on each collector tab (D6; up to 1.1 W in a 10 mA fault), 1.5 mm to everything; no thermal vias into L2.
DESIGN NOTE D1: 1 mA/V set by R7 = 1.00 k 0.1 % 25 ppm (0805 for self-heating). U2 INA149 senses across R7; U1 OPA192 buffers I_SENSE back to the REF pins (D-05).
DESIGN NOTE D2: Bias string and emitter followers Q1/Q2 (one BAS16 VBE each): PUMP_V+ / PUMP_V- float with PUMP_OUT; the INA149 needs >= 4.5 V across them. Compliance 5 mA into >= 13.1 kOhm at a 90 V rail [N].
LAYOUT NOTE L3: U2 straddles the HV/LV gap: inputs (pins 2, 3) face the LV zone; pin-to-pin creepage inside the package is excluded.
[7] Analog - Howland Current Pump
